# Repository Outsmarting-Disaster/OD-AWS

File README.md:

# OD-Automatic Weather Station

## Why are We Building OD-AWS?

## What is the OD-AWS?

## How does it work?

## Installation
Check out the [Wiki](https://github.com/Outsmarting-DIsaster/OD-AWS/wiki) to learn how to build your own Automatic Weather Station.

## Testing

From the project root, run the following snippet:

## Asembly

## How to Contribute

## License

This project is licensed under the MIT License - see the [LICENSE](LICENSE) file for details.

## Version

v1

[Outsmarting-Disaster]: <https://github.com/Outsmarting-Disaster>

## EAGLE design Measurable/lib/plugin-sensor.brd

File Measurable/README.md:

# Add on Measurable

Support DHT 22  & BMP 280

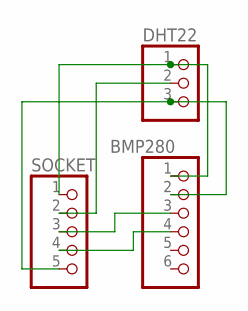
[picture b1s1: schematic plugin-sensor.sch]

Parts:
BMP280: PINHD-1X6/90; 1X06/90
DHT22: PINHD-1X3; 1X03
SOCKET: PINHD-1X5/90; 1X05/90

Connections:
unnamed: BMP280.1, DHT22.1, SOCKET.1
unnamed: BMP280.2, DHT22.3, SOCKET.5
unnamed: DHT22.2, SOCKET.2
unnamed: BMP280.3, SOCKET.3
unnamed: BMP280.4, SOCKET.4

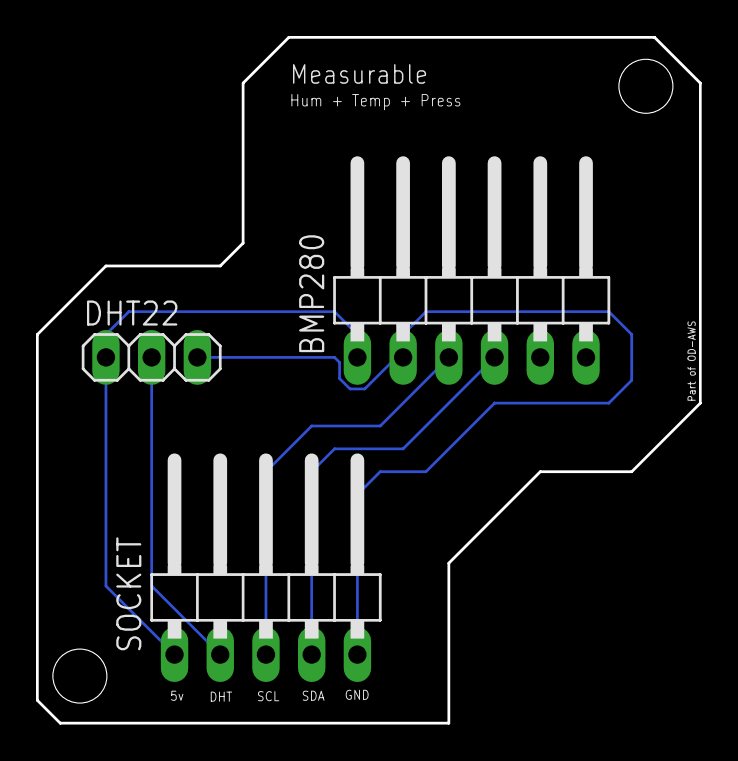
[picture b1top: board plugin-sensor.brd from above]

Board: 2 copper layers, 36.8 x 38.1 mm, 3 parts (0 on the bottom side), 5 nets.

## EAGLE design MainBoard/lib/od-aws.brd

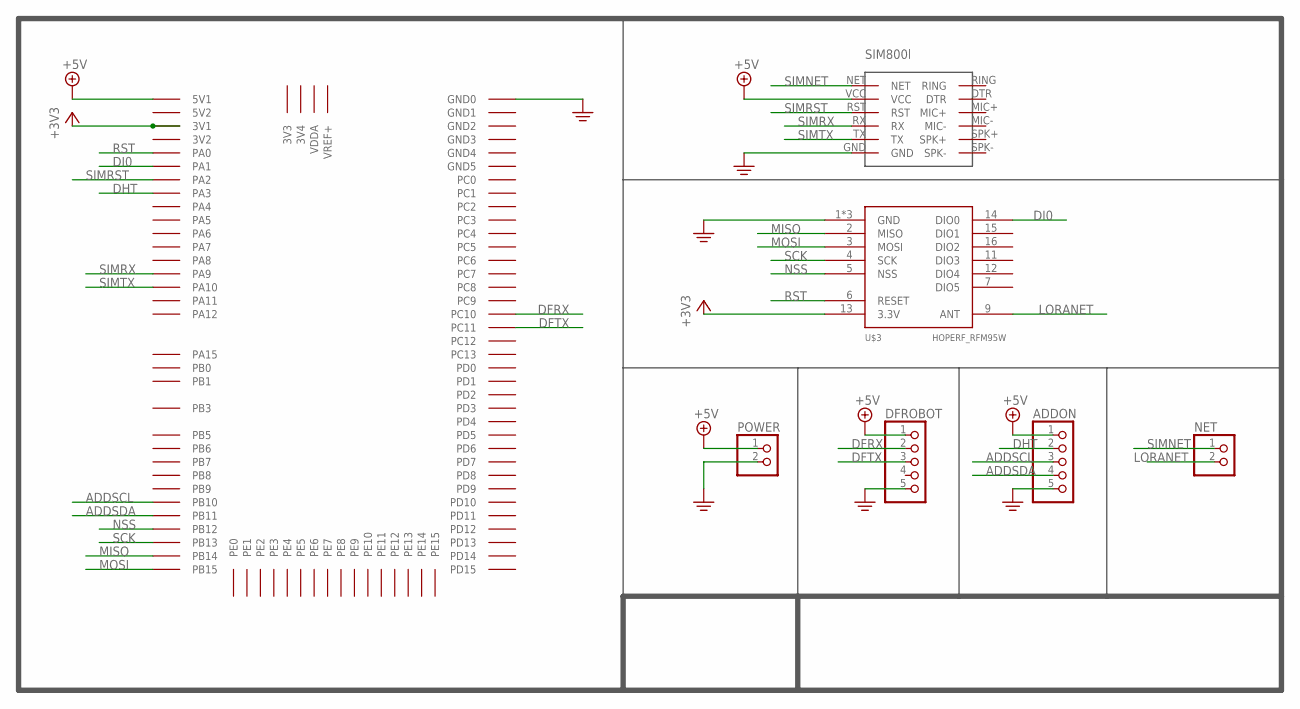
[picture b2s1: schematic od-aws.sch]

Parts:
ADDON: PINHD-1X5/90; 1X05/90
DFROBOT: PINHD-1X5/90; 1X05/90
NET: PINHD-1X2/90; 1X02/90
POWER: PINHD-1X2/90; 1X02/90
U$1: STM32F407VGT6
U$2: SIM800L-V1
U$3: HOPERF_RFM95W

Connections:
+3V3: U$1.3V31 (3V1), U$3.13 (3.3V)
+5V: ADDON.1, DFROBOT.1, POWER.1, U$1.5V1, U$2.VCC
ADDSCL: ADDON.3, U$1.PB10
ADDSDA: ADDON.4, U$1.PB11
DFRX: DFROBOT.2, U$1.PC10
DFTX: DFROBOT.3, U$1.PC11
DHT: ADDON.2, U$1.PA3
DI0: U$1.PA1, U$3.14 (DIO0)
LORANET: NET.2, U$3.9 (ANT)
MISO: U$1.PB14, U$3.2 (MISO)
MOSI: U$1.PB15, U$3.3 (MOSI)
NSS: U$1.PB12, U$3.5 (NSS)
PE: ADDON.5, DFROBOT.5, POWER.2, U$1.GND1 (GND0), U$2.GND, U$3.1 (GND), U$3.8 (GND), U$3.10 (GND)
RST: U$1.PA0, U$3.6 (RESET)
SCK: U$1.PB13, U$3.4 (SCK)
SIMNET: NET.1, U$2.NET
SIMRST: U$1.PA2, U$2.RST
SIMRX: U$1.PA9, U$2.RX
SIMTX: U$1.PA10, U$2.TX

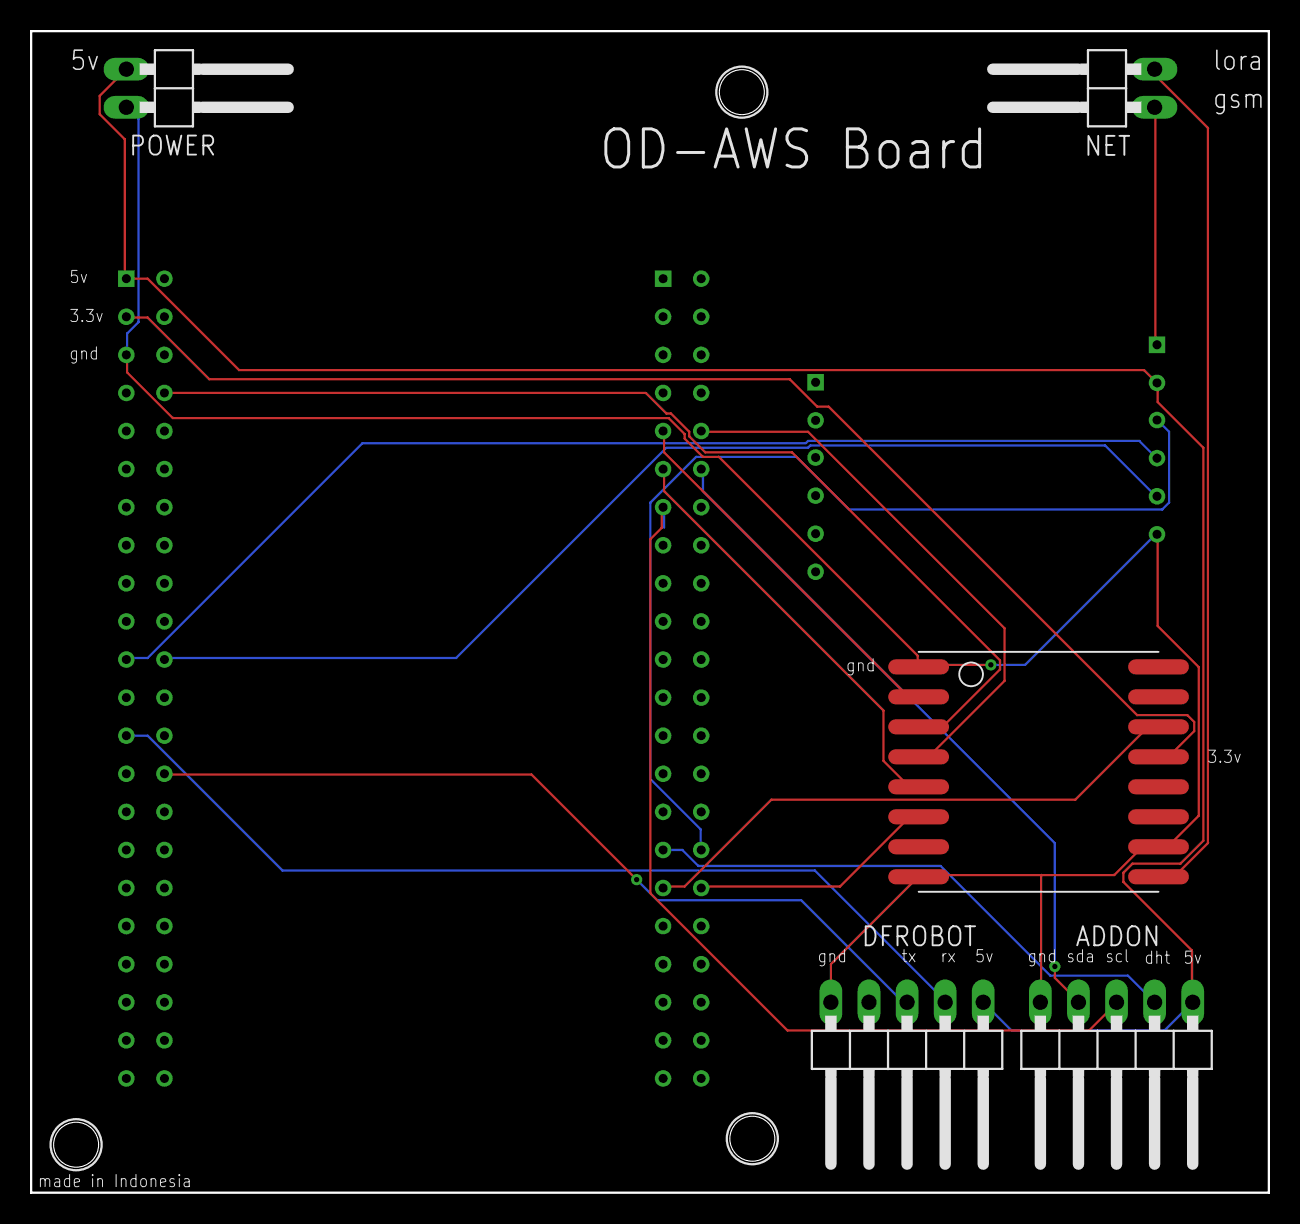
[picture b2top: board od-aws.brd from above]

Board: 2 copper layers, 82.5 x 77.5 mm, 7 parts (1 on the bottom side), 19 nets.

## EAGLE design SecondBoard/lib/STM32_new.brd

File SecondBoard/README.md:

# Mini Board OD-AWS

support stm32f401 Black Pill

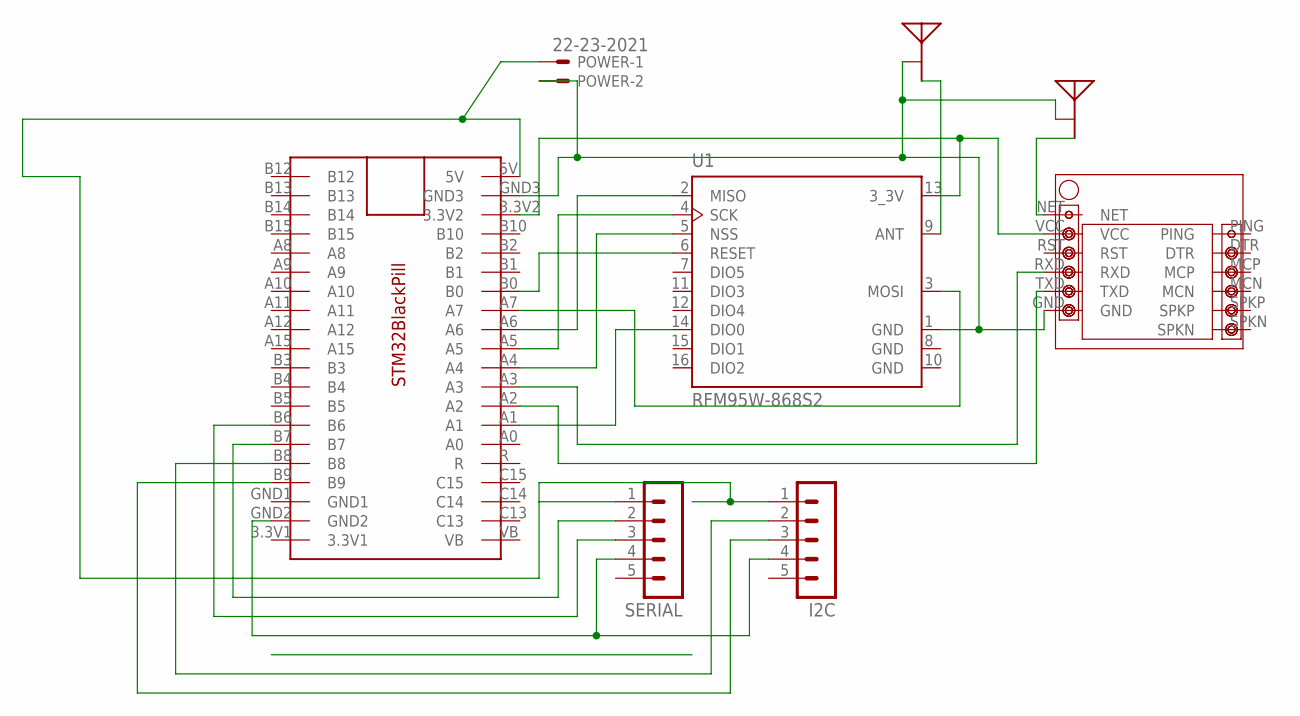
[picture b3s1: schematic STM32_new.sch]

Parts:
I2C: MA05-1
POWER: 22-23-2021
SERIAL: MA05-1
SIM800L_NEW1: SIM800L_NEW
U1: RFM95W-868S2; XCVR_RFM95W-868S2
U$1: STM32BLACKPILL
U$2, U$3: CHIP; 2450AT18B100

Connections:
unnamed: I2C.1, POWER.1, SERIAL.1, U$1.5V
unnamed: POWER.2, SIM800L_NEW1.GND, U1.1 (GND), U$1.GND3, U$2.GND, U$3.GND
unnamed: U1.6 (RESET), U$1.B0
unnamed: U1.4 (SCK), U$1.A5
unnamed: U1.2 (MISO), U$1.A6
unnamed: U1.3 (MOSI), U$1.A7
unnamed: U1.5 (NSS), U$1.A4
unnamed: U1.14 (DIO0), U$1.A1
unnamed: SIM800L_NEW1.TXD, U$1.A2
unnamed: SIM800L_NEW1.RXD, U$1.A3
unnamed: U1.9 (ANT), U$2.FEED
unnamed: SIM800L_NEW1.NET, U$3.FEED
unnamed: SIM800L_NEW1.VCC, U1.13 (3_3V), U$1.3.3V2
unnamed: SERIAL.2, U$1.B7
unnamed: SERIAL.3, U$1.B6
unnamed: I2C.4, SERIAL.4, U$1.GND2
unnamed: I2C.2, U$1.B8
unnamed: I2C.3, U$1.B9
WE: U1.8 (GND), U1.10 (GND)

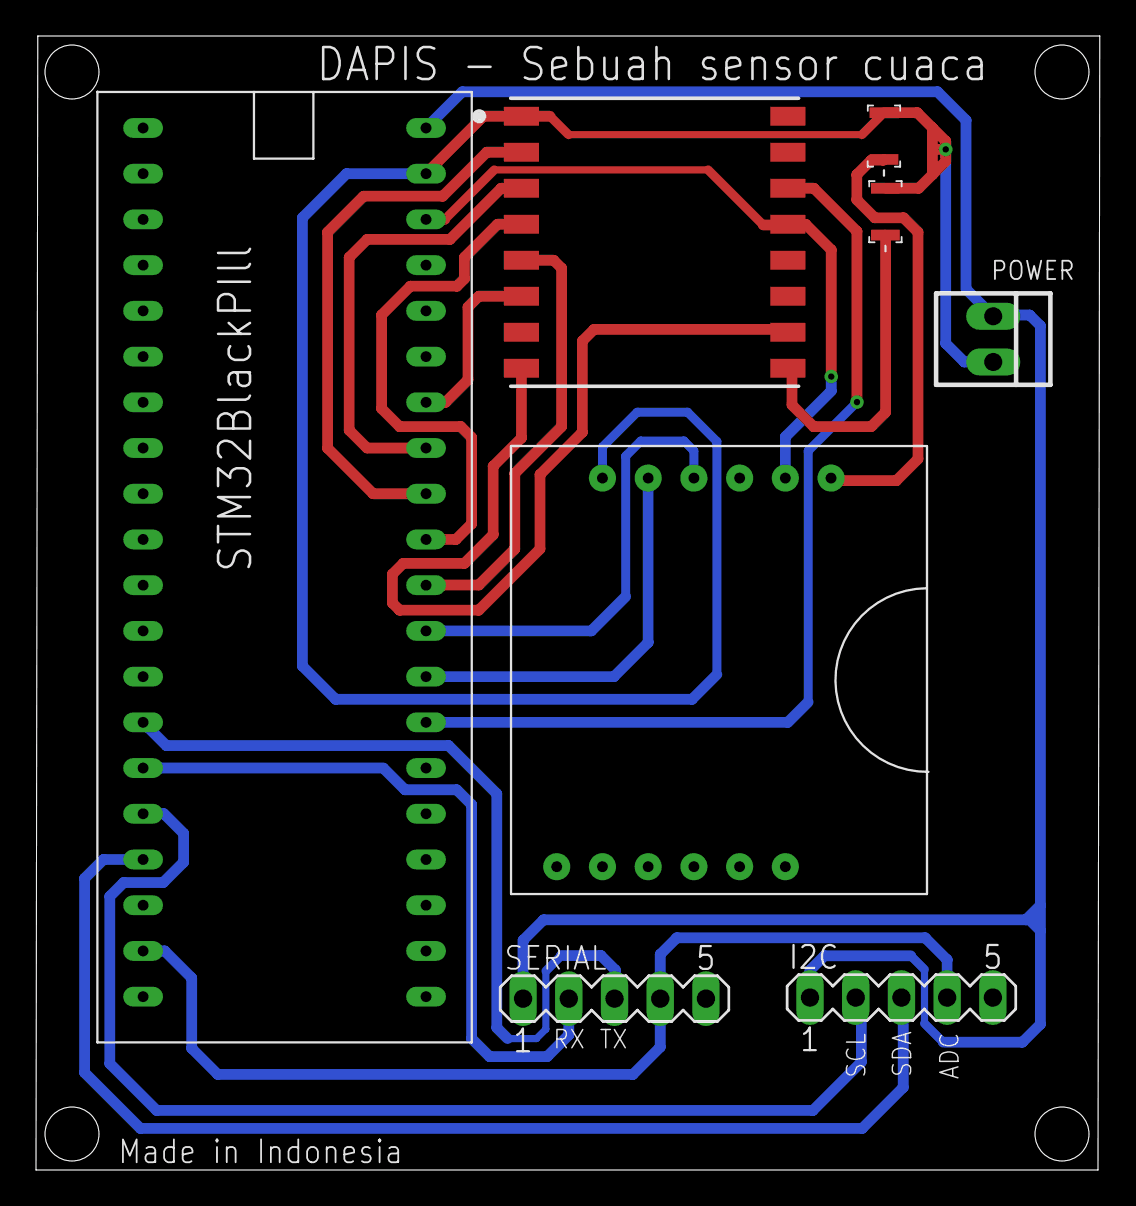
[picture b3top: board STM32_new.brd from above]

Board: 2 copper layers, 59.1 x 63.0 mm, 8 parts (0 on the bottom side), 19 nets.

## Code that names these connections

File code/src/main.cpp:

#include <ArduinoJson.h>
#include <SoftwareSerial.h>
#include <HardwareSerial.h>
#include <virtuabotixRTC.h>
#include <LoRa.h>
#include <SPI.h>
#include "SIM800L.h"
#include "STM32SD.h"

// Inisialisasi pin LoRa
#define SCK PB13  // GPIO  -- SX1278's SCK
#define MISO PB14 // GPIO -- SX1278's MISnO
#define MOSI PB15 // GPIO -- SX1278's MOSI
#define SS PB12   // GPIO -- SX1278's CS
#define RST PA0   // GPIO -- SX1278's RESET
#define DI0 PA1   // GPIO -- SX1278's IRQ(Interrupt Request)
#define BAND 915E6
String dataLoraReceive = "";
// end Lora

// Inisialisasi  RTC (CLK, DAT, RST)
virtuabotixRTC myRTC(PB10, PB11, PA3);

// Inisialisasi sim800l
#define SIM800_RX_PIN PA9
#define SIM800_TX_PIN PA10
#define SIM800_RST_PIN PA2

const char APN[] = "M2MAUTOTRONIC";
const char URL[] = "http://postman-echo.com/post";
const char CONTENT_TYPE[] = "application/json";
char PAYLOAD[400] = "";

SIM800L *sim800l;
SoftwareSerial sm(SIM800_RX_PIN, SIM800_TX_PIN);
// end Sim800l

// Inisialisasi dfRobot
static const int RXPin = PC10, TXPin = PC11;
char databuffer[35];
double temp;
int var = 1;
static const uint32_t dfBaud = 9600;
SoftwareSerial df(RXPin, TXPin);
// end df

// global
HardwareSerial Serial2(PD6, PD5);
int counter = 0;
#ifndef SD_DETECT_PIN
#define SD_DETECT_PIN SD_DETECT_NONE
#endif
File myFile;

void getBuffer() // Get weather status data
{
  int index;
  for (index = 0; index < 35; index++)
  {
    if (df.available())
    {
      databuffer[index] = df.read();
      if (databuffer[0] != 'c')
      {
        index = -1;
      }
    }
    else
    {
      index--;
    }
  }
}
int transCharToInt(char *_buffer, int _start, int _stop) // char to int）
{
  int _index;
  int result = 0;
  int num = _stop - _start + 1;
  int _temp[num];
  for (_index = _start; _index <= _stop; _index++)
  {
    _temp[_index - _start] = _buffer[_index] - '0';
    result = 10 * result + _temp[_index - _start];
  }
  return result;
}

int WindDirection() // Wind Direction
{
  return transCharToInt(databuffer, 1, 3);
}

float WindSpeedAverage() // air Speed (1 minute)
{
  temp = 0.44704 * transCharToInt(databuffer, 5, 7);
  return temp;
}

float WindSpeedMax() // Max air speed (5 minutes)
{
  temp = 0.44704 * transCharToInt(databuffer, 9, 11);
  return temp;
}

float Temperature() // Temperature ("C")
{
  temp = (transCharToInt(databuffer, 13, 15) - 32.00) * 5.00 / 9.00;
  return temp;
}

float RainfallOneHour() // Rainfall (1 hour)
{
  temp = transCharToInt(databuffer, 17, 19) * 25.40 * 0.01;
  return temp;
}

float RainfallOneDay() // Rainfall (24 hours)
{
  temp = transCharToInt(databuffer, 21, 23) * 25.40 * 0.01;
  return temp;
}

int Humidity() // Humidity
{
  return transCharToInt(databuffer, 25, 26);
}

float BarPressure() // Barometric Pressure
{
  temp = transCharToInt(databuffer, 28, 32);
  return temp / 10.00;
}

void loop_dfrobot()
{
  Serial2.println("Start DF Robot");
  // getBuffer(); // Begin
  StaticJsonDocument<200> doc;
  doc["id"] = "1";
  doc["windDirection"] = WindDirection();
  doc["averageWindSpeed"] = WindSpeedAverage();
  doc["maxWindSpeed"] = WindSpeedMax();
  doc["rainFallOneHour"] = RainfallOneHour();
  doc["rainFallOneHour"] = RainfallOneDay();
  doc["temprature"] = Temperature();
  doc["humidity"] = Humidity();
  doc["barometricPressure"] = BarPressure();
  doc["receiveLoraData"] = dataLoraReceive;
  doc["times"] = String(myRTC.dayofmonth) + String(myRTC.month) + String(myRTC.year) + String(myRTC.hours) + String(myRTC.minutes) + String(myRTC.seconds);
  serializeJsonPretty(doc, Serial2);
  serializeJson(doc, PAYLOAD);
  Serial2.println("");
}

void setupModule()
{
  // Wait until the module is ready to accept AT commands
  while (!sim800l->isReady())
  {
    Serial2.println(F("Problem to initialize AT command, retry in 1 sec"));
    delay(1000);
  }

  Serial2.println(F("Setup Complete!"));

  // Wait for the GSM signal
  uint8_t signal = sim800l->getSignal();
  while (signal <= 0)
  {
    delay(1000);
    signal = sim800l->getSignal();
  }
  Serial2.print(F("Signal OK (strenght: "));
  Serial2.print(signal);
  Serial2.println(F(")"));
  delay(1000);

  // Wait for operator network registration (national or roaming network)
  NetworkRegistration network = sim800l->getRegistrationStatus();
  while (network != REGISTERED_HOME && network != REGISTERED_ROAMING)
  {
    delay(1000);
    network = sim800l->getRegistrationStatus();
  }
  Serial2.println(F("Network registration OK"));
  delay(1000);

  // Setup APN for GPRS configuration
  bool success = sim800l->setupGPRS(APN);
  while (!success)
  {
    success = sim800l->setupGPRS(APN);
    delay(5000);
  }
  Serial2.println(F("GPRS config OK"));
}
void loop_sim800l(void)
{
  // Establish GPRS connectivity (5 trials)
  bool connected = false;
  for (uint8_t i = 0; i < 5 && !connected; i++)
  {
    delay(1000);
    connected = sim800l->connectGPRS();
  }

  // Check if connected, if not reset the module and setup the config again
  if (connected)
  {
    Serial2.print(F("GPRS connected with IP "));
    Serial2.println(sim800l->getIP());
  }
  else
  {
    Serial2.println(F("GPRS not connected !"));
    Serial2.println(F("Reset the module."));
    sim800l->reset();
    setupModule();
    return;
  }
  Serial2.println(F("Start HTTP POST..."));
  Serial2.println(PAYLOAD);
  // Do HTTP POST communication with 10s for the timeout (read and write)
  uint16_t rc = sim800l->doPost(URL, CONTENT_TYPE, PAYLOAD, 10000, 10000);
  if (rc == 200)
  {
    // Success, output the data received on the serial
    Serial2.print(F("HTTP POST successful ("));
    Serial2.print(sim800l->getDataSizeReceived());
    Serial2.println(F(" bytes)"));
    Serial2.print(F("Received : "));
    Serial2.println(sim800l->getDataReceived());
    var = 1;
  }
  else
  {
    // Failed...
    Serial2.print(F("HTTP POST error "));
    Serial2.println(rc);
    var = 3;
  }

  delay(1000);
}
void loop_loraSender()
{
  Serial2.println("Sending packet: ");
  LoRa.beginPacket();
  LoRa.print(PAYLOAD);
  LoRa.endPacket();
}

void setup()
{
  Serial2.begin(115200);
  LoRa.setSPIFrequency(2E6);
  pinMode(SS, OUTPUT);
  digitalWrite(SS, HIGH);
  SPI.setMISO(MISO);
  SPI.setMOSI(MOSI);
  SPI.setSCLK(SCK);
  SPI.setSSEL(SS);
  LoRa.setPins(SS, RST, DI0);
  while (!LoRa.begin(915E6))
  {
    Serial2.println("Lora Failed");
    delay(500);
  }
  Serial2.println("LoRa Initializing OK!");
  Serial2.print("Initializing SD card...");
  while (!SD.begin(SD_DETECT_NONE))
  {
    delay(10);
  }
  Serial2.println("initialization done.");

  // open the file. note that only one file can be open at a time,
  // so you have to close this one before opening another.
  myFile = SD.open("test2.txt", FILE_WRITE);

  // if the file opened okay, write to it:

  // get data lora
  //  seconds, minutes, hours, day of the week, day of the month, month, year
  // myRTC.setDS1302Time(40, 24, 20, 7, 10, 9, 2022);
}

void loop()
{
  myRTC.updateTime();
  int packetSize = LoRa.parsePacket();
  if (packetSize)
  {
    Serial.print("Recive data ");

    while (LoRa.available())
    {
      dataLoraReceive = LoRa.readString();
    }
  }
  else
  {
    dataLoraReceive = "";
  }
  switch (var)
  {
  case 1:
    // Inisialisasi df
    df.begin(9600);
    // setup lora

    delay(1000);
    // loop_loraReceiver();
    // get data df
    getBuffer();
    // call for more function
    loop_dfrobot();
    var = 2;
    break;
  case 2:
    sm.begin(115200);
    sim800l = new SIM800L((Stream *)&sm, SIM800_RST_PIN, 200, 512);
    setupModule();
    loop_sim800l();
    break;
  case 3:
    loop_loraSender();
    var = 1;
    break;
  default:
    break;
  }
  if (myFile)
  {
    Serial2.print("Writing to datalog.txt...");
    myFile.println(PAYLOAD);
    Serial2.println("done.");
  }
  else
  {
    // if the file didn't open, print an error:
    Serial2.println("error opening datalog.txt");
  }
}

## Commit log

2022-08-18 new component main board and add on
2022-08-19 uppdate docmentation
2022-08-19 upload gerber file
2022-08-19 update all board
2022-08-20 new documentation
2022-08-20 new version build
2022-08-20 clean code and repository
2022-08-20 update measurable sensor
2022-08-20 new gerber file
2022-08-20 preview board
2022-08-31 setup df & configure json
2022-09-02 update sch second board
2022-09-19 update new code
2022-09-19 new doc assets
